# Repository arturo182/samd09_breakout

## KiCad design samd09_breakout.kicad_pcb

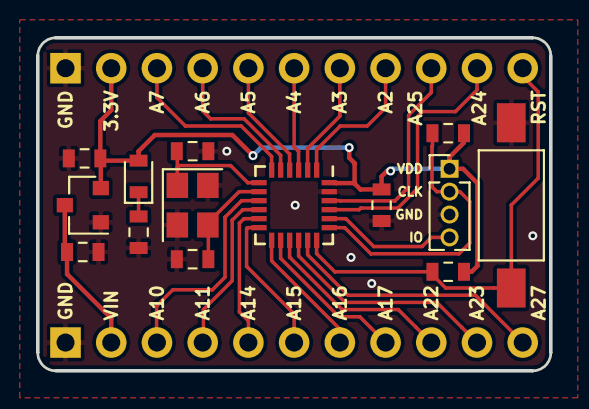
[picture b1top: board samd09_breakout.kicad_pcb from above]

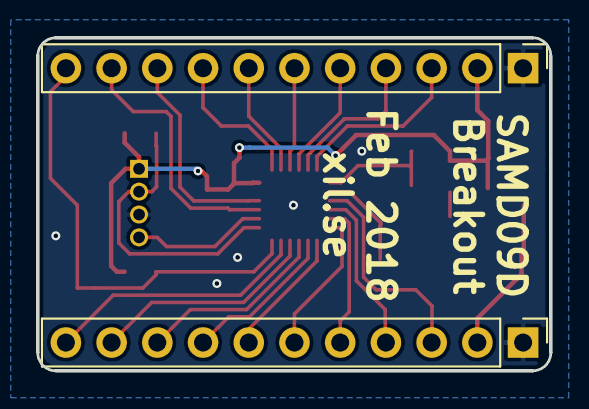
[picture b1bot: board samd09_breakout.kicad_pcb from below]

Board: 2 copper layers, 28.5 x 18.5 mm, 16 parts (2 on the bottom side), 26 nets.

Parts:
C1: 0.1uF; C_0603_1608Metric
C2, C3: 12pF; C_0603_1608Metric
C4, C5: 1uF; C_0603_1608Metric
D1: PWR; LED_0603_1608Metric
J1, J2: Conn_01x11; PinHeader_1x11_P2.54mm_Vertical
J3: Conn_01x04; PinHeader_1x04_P1.27mm_Vertical
R1: 10K; R_0603_1608Metric
R2: 360R; R_0603_1608Metric
R3: 1K; R_0603_1608Metric
SW1: RESET; SW_SPST_FSMSM
U1: ATSAMD09D14A-MUT; QFN-24_4x4mm_P0.5mm
U2: XC6206P332MR; SOT-23
Y1: 16MHz; Crystal_SMD_3225-4Pin_3.2x2.5mm

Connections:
+3V3: C1.1, C5.1, D1.2, J2.2, J3.1, R1.1, R3.2, U1.24, U2.2
/PA2: J2.8, U1.1
/PA3: J2.7, U1.2
/PA4: J2.6, U1.3
/PA5: J2.5, U1.4
/PA6: J2.4, U1.5
/PA7: J2.3, U1.6
/PA10: J1.3, U1.9
/PA11: J1.4, U1.10
/PA14: J1.5, U1.11
/PA15: J1.6, U1.12
/PA16: J1.7, U1.13
/PA17: J1.8, U1.14
/PA22: J1.9, U1.15
/PA23: J1.10, U1.16
/PA24: J2.10, U1.21
/PA25: J2.9, U1.22
/PA27: J1.11, U1.17
/RESET: J2.11, R1.2, SW1.2, U1.18
/SWDCLK: J3.2, R3.1, U1.19
/SWDIO: J3.4, U1.20
GND: C1.2, C2.2, C3.2, C4.1, C5.2, J1.1, J2.1, J3.3, R2.2, SW1.1, U1.23, U2.1, Y1.2, Y1.4
unnamed: C2.1, U1.7, Y1.1
unnamed: C3.1, U1.8, Y1.3
unnamed: D1.1, R2.1
VBUS: C4.2, J1.2, U2.3

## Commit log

2018-02-10 Initial import
